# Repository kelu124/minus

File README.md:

# minus

**A minimal, single-channel, low-cost, open-source ultrasound pulse-echo platform —
built as a conference-workshop badge.**

`minus` drives one piezo transducer with a high-voltage pulse, amplifies and digitizes
the returning echo, and streams the raw data to a host. It is designed to be **cheap,
small, simple, and hackable** — a badge attendees can use in an ultrasound-conference
workshop (e.g. **muscle-contraction monitoring**, A-/M-mode) and then extend and
experiment with (coded excitation, on-device DSP, add-on boards).

> ⚠️ **Status: early design.** This repository currently holds the **requirements,
> a survey of comparable systems, a component trade study, and reference designs** —
> not yet a finished board. Non-clinical, for **research / education / NDT** only;
> not a medical device.

## What it is (at a glance)

- **MCU:** Raspberry Pi **RP2350** — precise pulse timing + fast ADC capture via PIO.
- **Signal:** **3–4 MHz** piezo (provided with the kit), **raw RF** A-mode + M-mode.
- **Front end:** unipolar HV pulser (bipolar option) → T/R switch → VGA/TGC → external
  high-speed ADC. Reuses proven blocks from the author's open boards.
- **Badge:** on-board **USB-C** (host + power), **RGB LED + small OLED** for standalone
  display, **Raspberry-Pi 40-pin** extension header, transducer via **SMA / header / uFL**,
  friendly silkscreen + test points, OSHWA certification planned.
- **Open:** open hardware + firmware + host software; designed for JLCPCB fabrication.

## Repository map

| Path | What's there |
|------|--------------|
| [`requirements.md`](requirements.md) | The design requirements (MoSCoW), with open decisions. |
| [`analysis.md`](analysis.md) | Architecture analysis — integrated vs external-ADC routes; pulser and gain options. |
| [`options.md`](options.md) + [`options_prices.csv`](options_prices.csv) | Component trade study (pulser / gain / ADC) with LCSC-referenced pricing. |
| [`systems/`](systems/README.md) | Survey of ~19 comparable ultrasound systems (datasheets, literature, by-IC index). |
| [`design/`](design/README.md) | Reference design files (un0rick, lit3rick, pic0rick, Open Echo, BioGAP shield). |
| [`pdfs/`](pdfs/README.md) | Source papers and component datasheets. |
| [`docs/claude/`](docs/claude/README.md) | Working notes: session logs, decision memory, TODO/DONE, changelog. |

## Lineage & credits

`minus` builds on the open single-channel ultrasound work of **Luc Jonveaux (kelu124)** —
[echomods/Murgen](https://github.com/kelu124/echomods),
[un0rick](https://github.com/kelu124/un0rick),
[lit3rick](https://github.com/kelu124/lit3rick), and
[pic0rick](https://github.com/kelu124/pic0rick) — reusing their proven building blocks
to reduce risk. See [`systems/`](systems/README.md) for the broader field survey.

## License

Intended to be released as **open hardware + open software** (OSHWA certification
planned), following the licensing of the boards above.

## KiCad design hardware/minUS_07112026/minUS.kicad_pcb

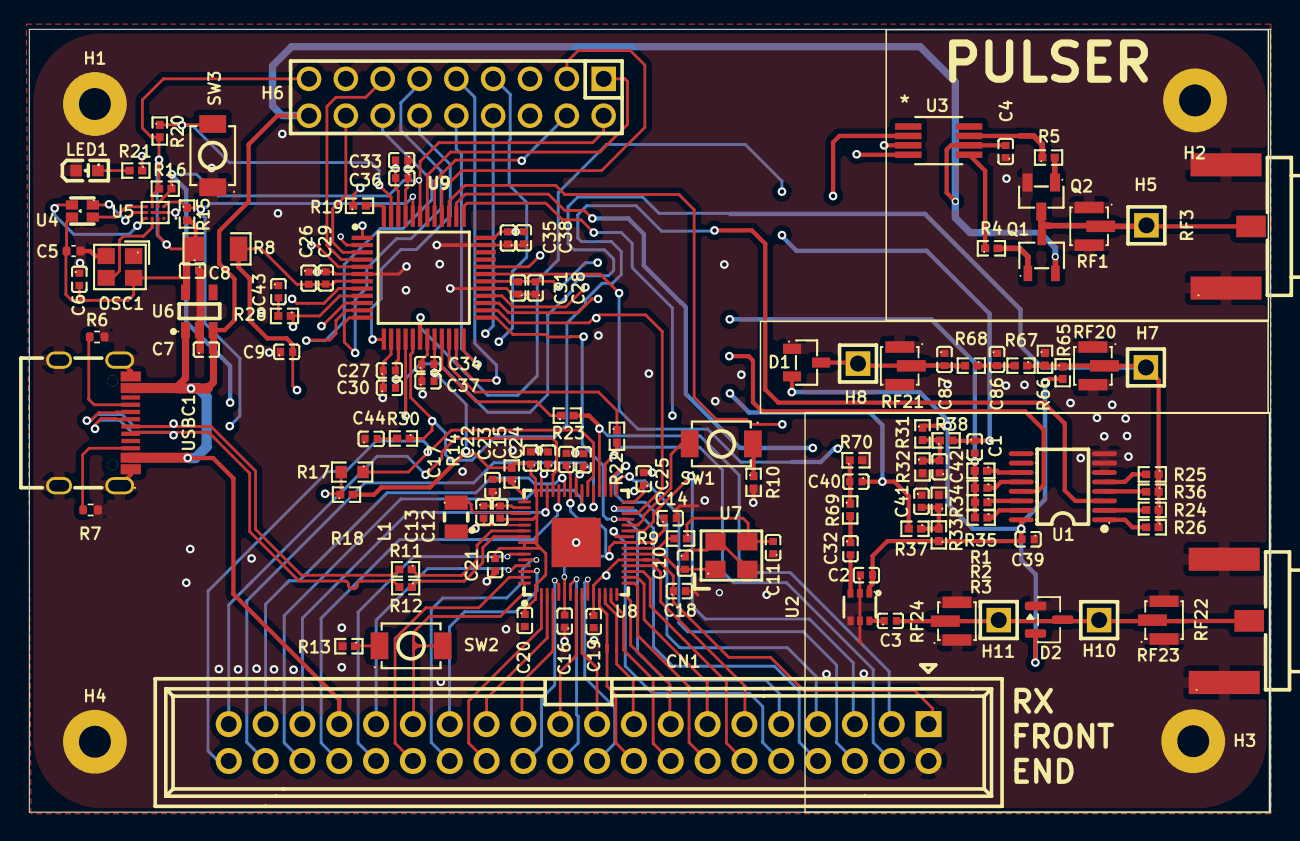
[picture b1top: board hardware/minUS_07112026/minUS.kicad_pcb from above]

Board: 4 copper layers, 85.6 x 54.0 mm, 126 parts (0 on the bottom side), 110 nets.

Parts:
C1, C3, C32, C40: CSA0402C0G331J500GT; C0402
C2: CC0402KRX7R9BB471; C0402
C4, C7, C8, C9: 1uF; C0402
C5: 4u7; C_0402_1005Metric
C6: 10nF; C0402
C10, C11: 15pF; C0402
C12, C13, C16, C17: 4.7uF; C0402
C14, C15, C18, C19, C20, C21, C22, C23, C24, C25, C26, C27, C28, C33, C34, C35, C39, C41, C42, C43, C44: 100nF; C0402
C29, C30, C31, C36, C37, C38: 1nF; C0402
C86, C87: 56pF; C0402
CN1: X9555WV-2X20-6TV01; IDC-TH_40P-P2.54_X9555WV-2X20-6TV01
D1: BAT54S_C916425; SOT-23-3_L2.9-W1.3-P1.90-LS2.4-BR
D2: BAV99; SOT-23
H1, H2, H3, H4: MountingHole_Pad; MountingHole_2.2mm_M2_Pad
H5, H7, H8, H10, H11: PZ254V-11-01P; HDR-TH_1P-P2.54-V-M
H6: PZ254V-12-18P; HDR-TH_18P-P2.54-V-M-R2-C9-S2.54
L1: 3.3uH; IND-SMD_L2.0-W1.6_AOTA-B201610S3R3-101-T
LED1: KT-0603R; LED-SMD_L1.6-W0.8-R-RD
OSC1: SX2M32.768KM20F30TNN; OSC-SMD_4P-L2.5-W2.0-BL
Q1: IRLML2244TRPBF; SOT-23-3_L2.9-W1.6-P1.90-LS2.8-BR
Q2: IRLML6244TRPBF; SOT-23-3_L2.9-W1.3-P1.90-LS2.4-BR
R1, R26: RC0402FR-072K2L; R0402
R2, R25: RC0402FR-074K7L; R0402
R3, R24: FRC0402F6801TS; R0402
R4, R5: 10Ω; R0402
R6, R7: 5K1; R_0402_1005Metric
R8: 0Ω; R1206
R9, R10, R13: 1kΩ; R0402
R11, R12: 22Ω; R0402
R14: 33Ω; R0402
R15, R16, R18, R20, R31, R32, R33, R34, R35, R36, R37, R38, R65, R66, R69, R70: 10KΩ; R0402
R17: 4.7kΩ; R0603
R19: 442Ω; R0402
R21: 330Ω; R0402
R22, R23: 0Ω; R0402
R28, R30: 1KΩ; R0402
R67, R68: 100Ω; R0402
RF1, RF20, RF21, RF23, RF24: CONUFL001-SMD-T; IPEX-SMD_3P-L2.6-W2.6-LS3.0
RF3, RF22: 132414; SMA-SMD_132414
SW1, SW2, SW3: TS-1088-AR02016; SW-SMD_L3.9-W3.0-P4.45
U1: SN74HC4052PWR; TSSOP-16_L5.0-W4.3-P0.65-LS6.4-BL
U2: BGA2817,115; SC-70-6_L2.0-W1.3-P0.65-LS2.1-BR
U3: TC4427AEUA713; MSOP8_MC_MCH-M
U4: A-SP1943B1GHR6C-C01-2T; LED-SMD_4P-L1.6-W1.5-BL_A-SP1943B1GHR6C-C01-2T
U5: LP5562TMX/NOPB; DSBGA-12_L1.7-W1.3-R3-C4-P0.40-TL
U6: AP2112K-3.3TRG1; SOT-25-5_L2.9-W1.6-P0.95-LS2.8-BL
U7: 12MHz; OSC-SMD_4P-L3.2-W2.5-BL_SIT8008BI
U8: RP2354A; QFN-60_L7.0-W7.0-P0.40-TL-EP3.4
U9: PIC32AK1216GC41048-I_PT; QFP50P900X900X120-48N
USBC1: TYPE-C-31-M-12; USB-C_SMD-TYPE-C-31-M-12_1

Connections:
+1.1V: C13.2, C14.1, C15.1, C16.2, L1.2, U8.6 (DVDD), U8.23 (DVDD), U8.39 (DVDD), U8.50 (VREG_FB)
+3V3_AVDD: C2.2, C9.2, C26.2, C29.2, C39.2, D1.2 (K), D2.2, R8.2, R31.1, R33.1, R65.2, U1.16 (VCC), U2.1 (VCC), U9.7 (AVDD)
+3V3_DVDD: C5.2, C6.2, C8.2, C12.2, C18.1, C19.1, C20.1, C21.1, C22.1, C23.1, C24.1, C25.1, C27.2, C28.2, C30.2, C31.2, C33.2, C34.2, C35.2, C36.2, C37.2, C38.2, CN1.1, H6.17, OSC1.4 (VDD), R8.1, R14.2, R15.2, R16.2, R18.2, R20.2, U4.3, U5.A2 (VDD), U5.C3 (EN/VCC), U6.5 (VOUT), U8.1 (IOVDD), U8.11 (IOVDD), U8.20 (IOVDD), U8.30 (IOVDD), U8.38 (IOVDD), U8.44 (ADC_AVDD), U8.45 (IOVDD), U8.49 (VREG_VIN), U8.53 (USB_OTP_VDD), U8.54 (QSPI_IOVDD), U9.15 (VDD_1), U9.20 (VDD_2), U9.30 (VDD_3), U9.36 (VDD_4), U9.46 (VDD_5)
+5.0V: C4.2, C7.2, CN1.33, H6.18, Q1.2 (S), U3.6, U6.1 (VIN), U6.3 (EN), USBC1.A4B9 (VBUS), USBC1.B4A9 (VBUS)
/PIC32/MCLR: R19.2, U9.48 (~MCLR)
/RP2354A/BOOT: SW1.1, U8.26 (RUN)
/RP2354A/USB_DN: R11.1, U8.51 (USB_DM)
/RP2354A/USB_DP: R12.1, U8.52 (USB_DP)
B: U4.4, U5.A4 (B)
G: U4.1, U5.B4 (G)
GND: C2.1, C4.1, C5.1, C6.1, C7.1, C8.1, C9.1, C10.1, C11.1, C12.1, C13.1, C14.2, C15.2, C16.1, C17.1, C18.2, C19.2, C20.2, C21.2, C22.2, C23.2, C24.2, C25.2, C26.1, C27.1, C28.1, C29.1, C30.1, C31.1, C33.1, C34.1, C35.1, C36.1, C37.1, C38.1, C39.1, C41.1, C42.1, C43.1, C44.1, C86.1, C87.1, CN1.2, D1.1 (A), D2.1, H1.1 (1_1), H2.1 (1_1), H3.1 (1_1), H4.1 (1_1), H6.15, LED1.2 (K), OSC1.2 (GND), Q2.2 (S), R6.2, R7.2, R10.2, R13.2, R32.2, R34.2, R66.1, R70.2, RF1.2, RF1.3, RF3.1, RF3.3, RF3.4, RF3.5, RF20.2, RF20.3, RF21.2, RF21.3, RF22.1, RF22.3, RF22.4, RF22.5, RF23.2, RF23.3, RF24.2, RF24.3, SW3.2, U1.6 (~E), U1.7 (VEE), U1.8 (GND), U2.2 (GND2), U2.4 (GND1), U2.5 (GND2), U3.3, U5.B1 (ADDR_SEL1), U5.B2 (ADDR_SEL0), U5.B3 (GND), U6.2 (GND), U7.2 (GND), U7.4 (GND), U8.47 (VREG_PGND), U8.61 (EP), U9.6 (AVSS), U9.14 (VSS_1), U9.19 (VSS_2), U9.29 (VSS_3), U9.35 (VSS_4), U9.45 (VSS_5), USBC1.1 (EH), USBC1.2 (EH), USBC1.3 (EH), USBC1.4 (EH), USBC1.A1B12 (GND), USBC1.B1A12 (GND)
unnamed: C11.2, R9.1, U7.3
unnamed: C32.1, R69.2
unnamed: C41.2, R33.2, R34.1, R37.1
unnamed: C42.2, R31.2, R32.1, R38.1
unnamed: C43.2, R28.2
unnamed: C44.2, R30.2
unnamed: C86.2, R67.2, R68.1
unnamed: LED1.1 (A), R21.2
unnamed: OSC1.3 (OUTPUT), U5.A3 (CLK_32K)
unnamed: Q1.1 (G), R4.2
unnamed: Q2.1 (G), R5.2
unnamed: R4.1, U3.5
unnamed: R5.1, U3.7
unnamed: R10.1, SW1.2
unnamed: R13.1, SW2.2
unnamed: R17.2, R18.1, R19.1
unnamed: R1.1, U1.12 (1Y0)
unnamed: R2.1, U1.14 (1Y1)
unnamed: R3.1, U1.15 (1Y2)
unnamed: R35.1, U1.11 (1Y3)
unnamed: R26.2, U1.1 (2Y0)
unnamed: R25.2, U1.5 (2Y1)
unnamed: R24.2, U1.2 (2Y2)
unnamed: R36.2, U1.4 (2Y3)
unnamed: C3.1, U2.6 (RF_IN)
unnamed: C32.2, U2.3 (RF_OUT)
unnamed: C17.2, R14.1, U8.46 (VREG_AVDD)
unnamed: L1.1, U8.48 (VREG_LX)
unnamed: H6.9, U9.23 (AD1ANN2/AD1AN8/RP23/RB6)
unnamed: H6.13, U9.4 (AD2AN9/ISRC3/IBIAS3/RP9/RA8)
unnamed: H6.10, U9.24 (AD2ANN2/AD2AN8/RP24/IOMF0/RB7)
unnamed: H6.6, U9.28 (OSCI/CLKI/RP34/IOMF6/RC1)
unnamed: H6.5, U9.27 (OSCO/CLKO/RP33/IOMF5/RC0)
unnamed: H6.16, U9.3 (PGC2/DACOUT1/AD1AN7/AD2AN3/CMP1D/CMP2D/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)
unnamed: R21.1, U9.32 (RP38/PWM4L/RC5)
unnamed: R20.1, SW3.1, U9.47 (RP53/PCI22/RD4)
unnamed: H6.4, U9.41 (RP54/ASCL1/RD5)
unnamed: H6.1, U9.42 (RP55/ASDA1/RD6)
unnamed: H6.3, U9.40 (TDI/RP52/PWM1L/IOMD5/RD3)
unnamed: R6.1, USBC1.A5 (CC1)
unnamed: R7.1, USBC1.B5 (CC2)
OA1IN+: C40.1, R37.2, U9.10 (OA1IN+/AD1AN1/CMP1B/RP5/RA4)
OA1IN-: R28.1, U1.13 (1Z), U9.9 (OA1IN-/AD1ANN1/AD2AN0/RP4/RA3)
OA1OUT: C1.2, R1.2, R2.2, R3.2, R35.2, U9.8 (OA1OUT/AD1AN0/CMP1A/RP3/RA2)
OA2IN+: C1.1, R38.2, U9.18 (OA2IN+/AD2AN4/CMP2B/RP19/RB2)
OA2IN-: R30.1, U1.3 (2Z), U9.17 (TMS/OA2IN-/AD1AN4/AD2ANN1/RP18/RB1)
OA2OUT: H7.1 (1_1), R24.1, R25.1, R26.1, R36.1, R65.1, R66.2, R67.1, RF20.1, U9.16 (OA2OUT/AD2AN1/CMP2A/RP17/INT0/RB0)
OA3IN+: H6.12, U9.13 (OA3IN+/AD2AN2/CMP3B/RP22/RB5)
OA3IN-: H6.11, U9.12 (OA3IN-/AD1AN2/RP7/RA6)
OA3OUT: H6.14, U9.11 (OA3OUT/AD1AN3/CMP3A/RP6/RA5)
PGC1: R22.1, U9.22 (PGC1/AD2AN5/CMP2C/ISRC1/IBIAS1/RP21/SCL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)
PGD1: R23.1, U9.21 (PGD1/AN1P5/CMP1C/ISRC0/IBIAS0/RP20/SDA1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)
PIC32_ADC: C87.2, D1.3, H8.1 (1_1), R68.2, RF21.1, U9.5 (AD1ANN3/AD1AN9/RP10/RA9)
QSPI_SCLK: CN1.28, U8.56 (QSPI_SCLK)
QSPI_SD0: CN1.31, U8.57 (QSPI_SD0)
QSPI_SD1: CN1.30, U8.59 (QSPI_SD1)
QSPI_SD2: CN1.27, U8.58 (QSPI_SD2)
QSPI_SD3: CN1.32, U8.55 (QSPI_SD3)
QSPI_SS: CN1.29, SW2.1, U8.60 (QSPI_SS)
R: U4.2, U5.C4 (R)
RDY: CN1.20, U8.10 (GPIO7), U9.2 (AD1AN6/RP8/IOMF1/RA7)
RP2354 PIO-PWM_H: CN1.18, U3.2, U8.12 (GPIO8)
RP2354 PIO-PWM_L: CN1.17, U3.4, U8.13 (GPIO9)
RP2354_PWM: CN1.13, U8.17 (GPIO13)
RP_GPIO10: CN1.16, U8.14 (GPIO10)
RP_GPIO14: CN1.12, U8.18 (GPIO14)
RP_GPIO15: CN1.11, U8.19 (GPIO15)
RP_GPIO18: CN1.8, U8.29 (GPIO18)
RP_GPIO19: CN1.6, U8.31 (GPIO19)
RP_GPIO20: CN1.7, U8.32 (GPIO20)
RP_GPIO21: CN1.4, R22.2, U8.33 (GPIO21)
RP_GPIO22: CN1.3, R23.2, U8.34 (GPIO22)
RP_GPIO23: CN1.38, U8.35 (GPIO23)
RP_GPIO24: CN1.40, R17.1, U8.36 (GPIO24)
RP_GPIO25: CN1.36, U8.37 (GPIO25)
RP_GPIO26: CN1.37, U8.40 (GPIO26_ADC0)
RP_GPIO27: CN1.34, U8.41 (GPIO27_ADC1)
RP_GPIO28: CN1.39, U8.42 (GPIO28_ADC2)
RP_GPIO29: CN1.35, U8.43 (GPIO29_ADC3)
RX_NODE: C40.2, R69.1, R70.1
SCL: CN1.25, H6.2, R16.1, U5.C2 (SCL), U8.3 (GPIO1), U9.43 (RP56/ASCL2/IOMD7/IOMF4/RD7)
SDA: CN1.26, R15.1, U5.C1 (SDA), U8.2 (GPIO0), U9.44 (RP57/ASDA2/IOMD6/IOMF3/RD8)
SPI_CLK: CN1.23, U8.4 (GPIO2), U9.38 (TCK/RP50/PWM2L/IOMD3/RD1)
SPI_CS: CN1.21, U8.8 (GPIO5), U9.37 (RP49/PWM2H/IOMD2/RD0)
SPI_CS1: CN1.15, U8.15 (GPIO11)
SPI_CS2: CN1.14, U8.16 (GPIO12)
SPI_MISO: CN1.22, U8.7 (GPIO4), U9.31 (PGC3/RP35/PWM4H/RC2)
SPI_MOSI: CN1.24, U8.5 (GPIO3), U9.39 (TDO/RP51/PWM1H/IOMD4/RD2)
SWCLK: CN1.10, U8.24 (SWCLK)
SWDIO: CN1.5, U8.25 (SWDIO)
TRANSDUCER: C3.2, D2.3, H10.1 (1_1), H11.1 (1_1), RF22.2, RF23.1, RF24.1
TRIG: CN1.19, U8.9 (GPIO6), U9.1 (PGD2/AD2AN6/CMP3C/ISRC2/IBIAS2/RP1/SDA2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)
Transducer: H5.1 (1_1), Q1.3 (D), Q2.3 (D), RF1.1, RF3.2
UART_RX: H6.8, U8.28 (GPIO17), U9.26 (RP40/RC7)
UART_TX: CN1.9, H6.7, U8.27 (GPIO16), U9.25 (RP39/RC6)
USB_D+: R12.2, USBC1.A6 (DP1), USBC1.B6 (DP2)
USB_D-: R11.2, USBC1.A7 (DN1), USBC1.B7 (DN2)
XIN: C10.2, U7.1, U8.21 (XIN)
XOUT: R9.2, U8.22 (XOUT)

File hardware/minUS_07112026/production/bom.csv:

Designator,Footprint,Quantity,Value,LCSC Part #
"C1, C3, C32, C40",C0402,4,CSA0402C0G331J500GT,C48642894
"C10, C11",C0402,2,15pF,C326803
"C12, C13, C16, C17",C0402,4,4.7uF,C5718966
"C14, C15, C18, C19, C20, C21, C22, C23, C24, C25, C26, C27, C28, C33, C34, C35, C39, C41, C42, C43, C44",C0402,21,100nF,C152814
C2,C0402,1,CC0402KRX7R9BB471,C106207
"C29, C30, C31, C36, C37, C38",C0402,6,1nF,C14442
"C4, C7, C8, C9",C0402,4,1uF,C52923
C5,0402,1,4u7,C326586
C6,C0402,1,10nF,C15195
"C86, C87",C0402,2,56pF,C526981
CN1,IDC-TH_40P-P2.54_X9555WV-2X20-6TV01,1,X9555WV-2X20-6TV01,C2884558
D1,SOT-23-3_L2.9-W1.3-P1.90-LS2.4-BR,1,BAT54S_C916425,C916425
D2,SOT-23,1,BAV99,C2500
"H10, H11, H5, H7, H8",HDR-TH_1P-P2.54-V-M,5,PZ254V-11-01P,C492400
H6,HDR-TH_18P-P2.54-V-M-R2-C9-S2.54,1,PZ254V-12-18P,C492426
L1,IND-SMD_L2.0-W1.6_AOTA-B201610S3R3-101-T,1,3.3uH,C42411119
LED1,LED-SMD_L1.6-W0.8-R-RD,1,KT-0603R,C2286
OSC1,OSC-SMD_4P-L2.5-W2.0-BL,1,SX2M32.768KM20F30TNN,C2901603
Q1,SOT-23-3_L2.9-W1.6-P1.90-LS2.8-BR,1,IRLML2244TRPBF,C169763
Q2,SOT-23-3_L2.9-W1.3-P1.90-LS2.4-BR,1,IRLML6244TRPBF,C143946
"R1, R26",R0402,2,RC0402FR-072K2L,C114762
"R10, R13, R9",R0402,3,1kΩ,C2906864
"R11, R12",R0402,2,22Ω,C2929994
R14,R0402,1,33Ω,C2906931
"R15, R16, R18, R20, R31, R32, R33, R34, R35, R36, R37, R38, R65, R66, R69, R70",R0402,16,10KΩ,C25744
R17,R0603,1,4.7kΩ,C99782
R19,R0402,1,442Ω,C453691
"R2, R25",R0402,2,RC0402FR-074K7L,C105871
R21,R0402,1,330Ω,C105875
"R22, R23",R0402,2,0Ω,C844673
"R24, R3",R0402,2,FRC0402F6801TS,C2906876
"R28, R30",R0402,2,1KΩ,C11702
"R4, R5",R0402,2,10Ω,C138066
"R6, R7",0402,2,5K1,C105873
"R67, R68",R0402,2,100Ω,C25076
R8,R1206,1,0Ω,C2907406
"RF1, RF20, RF21, RF23, RF24",IPEX-SMD_3P-L2.6-W2.6-LS3.0,5,CONUFL001-SMD-T,C22418213
"RF22, RF3",SMA-SMD_132414,2,132414,C6363889
"SW1, SW2, SW3",SW-SMD_L3.9-W3.0-P4.45,3,TS-1088-AR02016,C720477
U1,TSSOP-16_L5.0-W4.3-P0.65-LS6.4-BL,1,SN74HC4052PWR,C22449643
U2,SC-70-6_L2.0-W1.3-P0.65-LS2.1-BR,1,"BGA2817,115",C2654187
U3,MSOP8_MC_MCH-M,1,TC4427AEUA713,C628548
U4,LED-SMD_4P-L1.6-W1.5-BL_A-SP1943B1GHR6C-C01-2T,1,A-SP1943B1GHR6C-C01-2T,C19171342
U5,DSBGA-12_L1.7-W1.3-R3-C4-P0.40-TL,1,LP5562TMX/NOPB,C544465
U6,SOT-25-5_L2.9-W1.6-P0.95-LS2.8-BL,1,AP2112K-3.3TRG1,C51118
U7,OSC-SMD_4P-L3.2-W2.5-BL_SIT8008BI,1,12MHz,C20625731
U8,QFN-60_L7.0-W7.0-P0.40-TL-EP3.4,1,RP2354A,C41378174
U9,QFP50P900X900X120-48N,1,PIC32AK1216GC41048-I_PT,C46545915
USBC1,USB-C_SMD-TYPE-C-31-M-12_1,1,TYPE-C-31-M-12,C165948

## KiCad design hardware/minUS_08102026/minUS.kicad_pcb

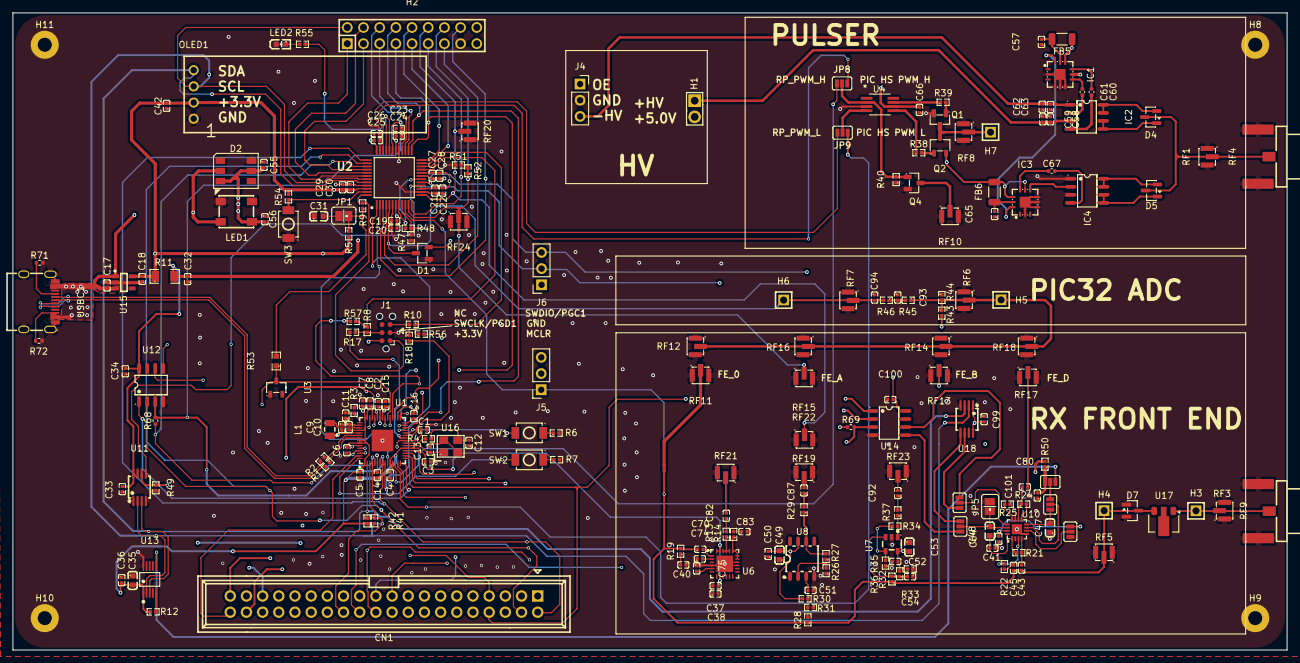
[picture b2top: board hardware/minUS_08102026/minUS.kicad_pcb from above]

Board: 4 copper layers, 200.0 x 100.0 mm, 222 parts (0 on the bottom side), 159 nets.

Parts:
C1, C2, C3, C4, C5, C6, C7, C8, C15, C16, C20, C21, C23, C25, C27, C29, C33, C34, C36, C37, C38, C41, C42, C50, C51, C52, C54, C55, C56, C57, C59, C63, C65, C70, C74, C75, C80, C82, C83, C87, C92, C99, C100, C101: 100nF; C0402
C9, C10, C11, C14: 4.7uF; C0402
C12, C13: 15pF; C0402
C17, C18, C32, C58, C62, C64, C66: 1uF; C0402
C19, C22, C24, C26, C28, C30: 1nF; C0402
C31: 470nF; C0603
C35, C49, C53: 10uF; C0603
C40: 47pF; C0402
C43, C45: 330nF; C0402
C47, C48: 2.2uF; C0603
C60, C61, C67: 10nF; C_0402_1005Metric
C93, C94: 56pF; C0402
CN1: X9555WV-2X20-6TV01; IDC-TH_40P-P2.54_X9555WV-2X20-6TV01
D1: BAT54S_C916425; SOT-23-3_L2.9-W1.3-P1.90-LS2.4-BR
D2: WS2812; LED_WS2812_PLCC6_5.0x5.0mm_P1.6mm
D4, D5, D7: BAV99; SOT-23
FB5, FB6: 120Ohm 3 A; L_1206_3216Metric
H1: PZ254V-11-02P; HDR-TH_2P-P2.54-V-M
H2: PZ254V-12-18P; HDR-TH_18P-P2.54-V-M-R2-C9-S2.54
H3, H4, H5, H6, H7: PZ254V-11-01P; HDR-TH_1P-P2.54-V-M
H8, H9, H10, H11: MountingHole_Pad; MountingHole_2.2mm_M2_Pad
IC1, IC3: MD1213K6-G; QFN-12_L4.0-W4.0-P0.80-BL-EP1.7
IC2, IC4: TC6320TG-G; SOIC-8_L4.9-W3.9-P1.27-LS6.0-BL
J1: Conn_ARM_SWD_TagConnect_TC2030-NL; Tag-Connect_TC2030-IDC-NL_2x03_P1.27mm_Vertical
J4, J5, J6: Conn_01x03_Pin; PinSocket_1x03_P2.54mm_Vertical
JP1, JP5: Jumper_2_Bridged; JUMPER_SMD_1x2
JP2, JP3, JP4, JP6, JP7, JP8, JP9: Jumper_3_Open; Jumper_3_NO
L1: 3.3uH; IND-SMD_L2.0-W1.6_AOTA-B201610S3R3-101-T
LED1: SK6812_C5378720; LED-SMD_4P-L5.4-W5.0_SK6812
LED2: KT-0603R; LED-SMD_L1.6-W0.8-R-RD
NT1, NT2: NetTie_2; NetTie-2_SMD_Pad0.5mm
OLED1: HS91L02W2C01; OLED-TH_L38.0-W12.0_HS91L02W2C01
Q1: IRLML6244TRPBF; SOT-23-3_L2.9-W1.3-P1.90-LS2.4-BR
Q2: IRLML2244TRPBF; SOT-23-3_L2.9-W1.6-P1.90-LS2.8-BR
Q4: 2N7002_C916396; SOT-23-3_L2.9-W1.3-P1.90-LS2.4-BR
R1, R2: 22Ω; R0402
R3: 33Ω; R0402
R4, R6, R7: 1kΩ; R0402
R5, R30, R31, R32, R33, R40, R41, R42, R43, R44, R48, R50, R52, R54: 10KΩ; R0402
R8, R10: 47Ω; R0402
R9: 442Ω; R0402
R11: 0Ω; R1206
R12: 100KΩ; R0402
R13, R14: 20Ω; R0402
R17, R18, R21, R22, R24, R25, R56, R57: 0Ω; R0402
R19: 15Ω; R0402
R26: 39.2Ω; R0402
R27: 750Ω; R0402
R28, R29, R36, R37: 50Ω; R0402
R34: 240Ω; R0402
R35: 27Ω; R0402
R38, R39: 10Ω; R0402
R45, R46: 100Ω; R0402
R47, R49, R51: 1KΩ; R0402
R53: 4.7kΩ; R0603
R55: 330Ω; R0402
R68, R69: 100R; R_0402_1005Metric
R71, R72: 5K1; R_0402_1005Metric
RF1, RF3, RF5, RF6, RF7, RF8, RF10, RF11, RF12, RF13, RF14, RF15, RF16, RF17, RF18, RF19, RF20, RF21, RF22, RF23, RF24: CONUFL001-SMD-T; IPEX-SMD_3P-L2.6-W2.6-LS3.0
RF4, RF9: 132414; SMA-SMD_132414
SW1, SW2, SW3: TS-1088-AR02016; SW-SMD_L3.9-W3.0-P4.45
U1: RP2354A; QFN-60_L7.0-W7.0-P0.40-TL-EP3.4
U2: PIC32AK1216GC41048-I_PT; QFP50P900X900X120-48N
U3: BAT54_C22466368; SOT-23-3_L2.9-W1.4-P1.90-LS2.5-BR
U4: TC4427AEUA713; MSOP8_MC_MCH-M
U6: AD8432ACPZ-R7; LFCSP-24_L4.0-W4.0-P0.50-BL-EP
U7: LMH6629MFX/NOPB; SOT-23-5_L2.9-W1.6-P0.95-LS2.8-BR
U8: OPA847IDR; SOIC-8_L4.9-W3.9-P1.27-LS6.0-TL
U10: AD8338ACPZ-RL; LFCSP-16_L3.0-W3.0-P0.50-BL-EP1.6
U11, U18: MCP4531-103E/MS; MSOP-8_L3.0-W3.0-P0.65-LS5.0-BL
U12, U14: MCP4131-104E/SN; SOIC-8_L4.9-W3.9-P1.27-LS6.0-BL
U13: MCP4728A0T-E/UN; MSOP-10_L3.0-W3.0-P0.50-LS5.0-BL
U15: AP2112K-3.3TRG1; SOT-25-5_L2.9-W1.6-P0.95-LS2.8-BL
U16: 12MHz; OSC-SMD_4P-L3.2-W2.5-BL_SIT8008BI
U17: MD0100N8-G; SOT-89-3
USBC1: TYPE-C-31-M-12; USB-C_SMD-TYPE-C-31-M-12_1

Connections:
+1.1V: C1.1, C2.1, C9.2, C14.2, L1.2, U1.6 (DVDD), U1.23 (DVDD), U1.39 (DVDD), U1.50 (VREG_FB)
+3V3_AVDD: C19.2, C20.2, C32.2, C33.2, C34.2, C64.2, C99.2, C100.2, D1.2 (K), JP2.3 (B), R11.2, R43.2, U2.7 (AVDD), U10.15 (VBAT), U11.8 (VDD), U12.8 (VDD), U14.8 (VDD), U18.1 (HVCA0), U18.8 (VDD)
+3V3_DVDD: C3.1, C4.1, C5.1, C6.1, C7.1, C8.1, C10.2, C15.1, C16.1, C18.2, C21.2, C22.2, C23.2, C24.2, C25.2, C26.2, C27.2, C28.2, C29.2, C30.2, C35.2, C36.2, C37.2, C38.1, C42.2, H2.17, J1.2 (VCC), OLED1.2 (VCC), R3.2, R5.2, R11.1, R12.1, R41.2, R42.2, R54.2, U1.1 (IOVDD), U1.11 (IOVDD), U1.20 (IOVDD), U1.30 (IOVDD), U1.38 (IOVDD), U1.44 (ADC_AVDD), U1.45 (IOVDD), U1.49 (VREG_VIN), U1.53 (USB_OTP_VDD), U1.54 (QSPI_IOVDD), U2.15 (VDD_1), U2.20 (VDD_2), U2.30 (VDD_3), U2.36 (VDD_4), U2.46 (VDD_5), U6.8 (VPS2), U6.23 (VPS1), U6.24 (ENB), U13.1 (VDD), U15.5 (VOUT)
+5.0V: C17.2, C49.2, C50.2, C52.2, C53.2, C55.2, C56.2, C66.2, D2.3 (VCC), D2.5 (VDD), FB5.1, FB6.1, H1.2, H2.18, IC1.8 (VH), IC1.10 (VDD2), IC3.8 (VH), IC3.10 (VDD2), LED1.3 (VDD), Q2.2 (S), R30.2, R32.2, U4.6, U7.5 (V+), U8.7 (+VS), U15.1 (VIN), U15.3 (EN), USBC1.A4B9 (VBUS), USBC1.B4A9 (VBUS)
+HV: C58.2, C59.2, H1.1, IC2.3 (SP)
-HV: C62.2, C63.2, IC2.1 (SN), J4.3
/PIC32/MCLR: J1.1 (~RESET), R9.2, U2.48 (~MCLR)
/RP2354A/BOOT: SW1.1, U1.26 (RUN)
/RP2354A/USB_DN: R2.1, U1.51 (USB_DM)
/RP2354A/USB_DP: R1.1, U1.52 (USB_DP)
FE_0_OUT: NT2.2, RF11.1
FE_A_OUT: J6.2, RF13.1, U2.16 (OA2OUT/AD2AN1/CMP2A/RP17/INT0/RB0), U11.5 (P0A)
FE_B_OUT: NT1.2, RF15.1
FE_D_OUT: C80.2, RF17.1
GND: C1.2, C2.2, C3.2, C4.2, C5.2, C6.2, C7.2, C8.2, C9.1, C10.1, C11.1, C12.1, C13.1, C14.1, C15.2, C16.2, C17.1, C18.1, C19.1, C20.1, C21.1, C22.1, C23.1, C24.1, C25.1, C26.1, C27.1, C28.1, C29.1, C30.1, C31.1, C32.1, C33.1, C34.1, C35.1, C36.1, C37.1, C38.2, C40.1, C41.1, C42.1, C47.1, C49.1, C50.1, C51.1, C52.1, C53.1, C54.1, C55.1, C56.1, C57.1, C58.1, C59.1, C62.1, C63.1, C64.1, C65.1, C66.1, C74.1, C75.1, C83.2, C93.1, C94.1, C99.1, C100.1, C101.1, D1.1 (A), D2.6 (VSS), D7.1, D7.2, H2.15, H8.1 (1_1), H9.1 (1_1), H10.1 (1_1), H11.1 (1_1), IC1.2 (VL), IC1.4 (GND_1), IC1.5 (VSS1), IC1.6 (VSS2), IC1.13 (GND_2), IC3.2 (VL), IC3.4 (GND_1), IC3.5 (VSS1), IC3.6 (VSS2), IC3.13 (GND_2), IC4.1 (SN), IC4.3 (SP), J1.3 (GND), J4.2, JP2.1 (A), JP5.1 (A), LED1.1 (GND), LED2.2 (K), OLED1.1 (GND), Q1.2 (S), Q4.2 (S), R6.2, R7.2, R26.1, R31.1, R33.1, R35.1, R40.1, R44.1, R47.2, R49.2, R51.2, R71.2, R72.2, RF1.2, RF1.3, RF3.2, RF3.3, RF4.1, RF4.3, RF4.4, RF4.5, RF5.2, RF5.3, RF6.2, RF6.3, RF7.2, RF7.3, RF8.2, RF8.3, RF9.1, RF9.3, RF9.4, RF9.5, RF10.2, RF10.3, RF11.2, RF11.3, RF12.2, RF12.3, RF13.2, RF13.3, RF14.2, RF14.3, RF15.2, RF15.3, RF16.2, RF16.3, RF17.2, RF17.3, RF18.2, RF18.3, RF19.2, RF19.3, RF20.2, RF20.3, RF21.2, RF21.3, RF22.2, RF22.3, RF23.2, RF23.3, RF24.2, RF24.3, SW3.2, U1.47 (VREG_PGND), U1.61 (EP), U2.6 (AVSS), U2.14 (VSS_1), U2.19 (VSS_2), U2.29 (VSS_3), U2.35 (VSS_4), U2.45 (VSS_5), U3.1 (A), U4.3, U6.4 (COMM), U6.15 (COM2), U6.16 (COM1), U6.25 (EP), U7.2 (V-), U8.4 (–VS), U10.5 (COMM), U10.17 (EP), U11.1 (HVCA0), U11.4 (VSS), U12.4 (VSS), U13.10 (VSS), U14.4 (VSS), U15.2 (GND), U16.2 (GND), U16.4 (GND), U18.4 (VSS), USBC1.1 (EH), USBC1.2 (EH), USBC1.3 (EH), USBC1.4 (EH), USBC1.A1B12 (GND), USBC1.B1A12 (GND)
MCP4531_POW: J6.3, R49.1, U2.17 (TMS/OA2IN-/AD1AN4/AD2ANN1/RP18/RB1), U11.6 (P0W)
MCP4728_VOUTA: JP4.3 (B), U13.6 (VOUTA)
unnamed: C12.2, R4.1, U16.3
unnamed: C40.2, R19.1
unnamed: C45.2, R22.2
unnamed: C82.1, R13.2
unnamed: C82.2, RF21.1
unnamed: C83.1, R14.2
unnamed: C87.1, R29.2
unnamed: C87.2, RF22.1
unnamed: C92.1, R37.2
unnamed: C92.2, RF23.1
unnamed: C93.2, R45.2, R46.1
unnamed: D4.2 (A), IC2.7 (DN_1), IC2.8 (DN_2)
unnamed: D4.3 (K), D5.3 (K), RF1.1, RF4.2
unnamed: D5.2 (A), IC4.7 (DN_1), IC4.8 (DN_2)
unnamed: H5.1 (1_1), R43.1, R44.2, R45.1, RF6.1, RF12.1, RF14.1, RF16.1, RF18.1
unnamed: C60.1, IC1.9 (OUTA)
unnamed: C61.1, IC1.7 (OUTB)
unnamed: C57.2, FB5.2, IC1.11 (VDD1)
unnamed: D4.1 (K), IC2.5 (DP_1), IC2.6 (DP_2)
unnamed: C61.2, IC2.2 (GN)
unnamed: C60.2, IC2.4 (GP)
unnamed: C67.1, IC3.9 (OUTA)
unnamed: IC3.7 (OUTB), IC4.2 (GN)
unnamed: C65.2, FB6.2, IC3.11 (VDD1)
unnamed: D5.1 (K), IC4.5 (DP_1), IC4.6 (DP_2)
unnamed: C67.2, IC4.4 (GP)
unnamed: J1.4 (SWCLK), R8.2, R17.1
unnamed: J1.5 (SWDIO), R10.2, R18.1
unnamed: C31.2, JP1.1 (A)
unnamed: JP1.2 (B), R5.1, R9.1, R53.2
unnamed: JP2.2 (C), U10.6 (MODE)
unnamed: C47.2, JP3.1 (A), U10.8 (DETO)
unnamed: JP3.3 (B), JP4.2 (C)
unnamed: JP3.2 (C), U10.7 (GAIN)
unnamed: C48.1, JP5.2 (B), JP7.2 (C), U10.14 (NOFSN)
unnamed: JP6.1 (A), U18.6 (P0W)
unnamed: JP6.3 (B), U14.6 (P0W)
unnamed: JP6.2 (C), U10.13 (VAGC)
unnamed: JP7.1 (A), U18.5 (P0A)
unnamed: JP7.3 (B), U14.5 (P0A)
unnamed: JP8.2 (C), Q4.1 (G), R40.2, U4.2
unnamed: JP9.2 (C), U4.4
unnamed: LED2.1 (A), R55.2
unnamed: Q1.1 (G), R39.2
unnamed: Q2.1 (G), R38.2
unnamed: Q4.3 (D), RF10.1
unnamed: R6.1, SW1.2
unnamed: R7.1, SW2.2
unnamed: R38.1, U4.5
unnamed: R39.1, U4.7
unnamed: CN1.3, U1.18 (GPIO14)
unnamed: CN1.5, U1.19 (GPIO15)
unnamed: CN1.11, U1.29 (GPIO18)
unnamed: CN1.13, U1.31 (GPIO19)
unnamed: CN1.15, U1.32 (GPIO20)
unnamed: CN1.21, U1.35 (GPIO23)
unnamed: CN1.25, U1.37 (GPIO25)
unnamed: CN1.27, U1.40 (GPIO26_ADC0)
unnamed: CN1.29, U1.41 (GPIO27_ADC1)
unnamed: CN1.31, U1.42 (GPIO28_ADC2)
unnamed: CN1.33, U1.43 (GPIO29_ADC3)
unnamed: C11.2, R3.1, U1.46 (VREG_AVDD)
unnamed: L1.1, U1.48 (VREG_LX)
unnamed: H2.9, U2.23 (AD1ANN2/AD1AN8/RP23/RB6)
unnamed: H2.13, U2.4 (AD2AN9/ISRC3/IBIAS3/RP9/RA8)
unnamed: H2.10, U2.24 (AD2ANN2/AD2AN8/RP24/IOMF0/RB7)
unnamed: H2.6, U2.28 (OSCI/CLKI/RP34/IOMF6/RC1)
unnamed: H2.5, U2.27 (OSCO/CLKO/RP33/IOMF5/RC0)
unnamed: H2.16, U2.3 (PGC2/DACOUT1/AD1AN7/AD2AN3/CMP1D/CMP2D/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)
unnamed: R55.1, U2.32 (RP38/PWM4L/RC5)
unnamed: R54.1, SW3.1, U2.47 (RP53/PCI22/RD4)
unnamed: H2.4, U2.41 (RP54/ASCL1/RD5)
unnamed: H2.1, U2.42 (RP55/ASDA1/RD6)
unnamed: H2.3, U2.40 (TDI/RP52/PWM1L/IOMD5/RD3)
unnamed: R13.1, U6.20 (GMH1), U6.21 (GOH1), U6.22 (OPH1)
unnamed: R14.1, U6.17 (OPL1), U6.18 (GOL1), U6.19 (GML1)
unnamed: C70.2, U6.1 (INH1)
unnamed: C74.2, U6.2 (INL1)
unnamed: C75.2, U6.5 (INL2)
unnamed: C54.2, R32.1, R33.2, R36.2, U7.3 (+IN)
unnamed: R34.1, R35.2, U7.4 (-IN)
unnamed: R34.2, R37.1, U7.1 (OUT)
unnamed: R26.2, R27.1, U8.2 (Inverting/Input)
unnamed: C51.2, R28.2, R30.1, R31.2, U8.3 (Noninverting/Input)
unnamed: R27.2, R29.1, U8.6 (Output)
unnamed: R24.2, U10.9 (FBKM)
unnamed: R25.2, U10.12 (FBKP)
unnamed: R22.1, U10.3 (INMD)
unnamed: C43.2, R21.2, U10.4 (INMR)
unnamed: R21.1, U10.1 (INPR)
unnamed: C80.1, R24.1, U10.10 (OUTM)
unnamed: R25.1, U10.11 (OUTP)
unnamed: C41.2, C48.2, U10.16 (VREF)
unnamed: R71.1, USBC1.A5 (CC1)
unnamed: R72.1, USBC1.B5 (CC2)
OA1IN+: C43.1, C45.1, C70.1, D7.3, H4.1 (1_1), J5.1, NT2.1, R19.2, R28.1, R36.1, RF5.1, U2.10 (OA1IN+/AD1AN1/CMP1B/RP5/RA4), U17.3 (B)
OA1IN-: J5.2, R47.1, R48.2, U2.9 (OA1IN-/AD1ANN1/AD2AN0/RP4/RA3)
OA1OUT: J5.3, J6.1, R48.1, U2.8 (OA1OUT/AD1AN0/CMP1A/RP3/RA2), U2.18 (OA2IN+/AD2AN4/CMP2B/RP19/RB2)
OA3IN+: H2.12, RF19.1, RF20.1, U2.13 (OA3IN+/AD2AN2/CMP3B/RP22/RB5)
OA3IN-: H2.11, R51.1, R52.2, U2.12 (OA3IN-/AD1AN2/RP7/RA6)
OA3OUT: H2.14, NT1.1, R52.1, RF24.1, U2.11 (OA3OUT/AD1AN3/CMP3A/RP6/RA5)
OE: IC1.12 (OE), IC3.12 (OE), J4.1
PGC1: R10.1, R56.1, U2.22 (PGC1/AD2AN5/CMP2C/ISRC1/IBIAS1/RP21/SCL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)
PGD1: R8.1, R57.1, U2.21 (PGD1/AN1P5/CMP1C/ISRC0/IBIAS0/RP20/SDA1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)
PIC32_ADC: C94.2, D1.3, H6.1 (1_1), R46.2, RF7.1, U2.5 (AD1ANN3/AD1AN9/RP10/RA9)
PIC HS-PWM_H: JP8.1 (A), U2.33 (PGD3/RP36/PWM3H/IOMD0/RC3)
PIC HS-PWM_L: JP9.1 (A), U2.34 (RP37/PWM3L/IOMD1/RC4)
QSPI_SCLK: CN1.35, U1.56 (QSPI_SCLK)
QSPI_SD0: CN1.38, U1.57 (QSPI_SD0)
QSPI_SD1: CN1.40, U1.59 (QSPI_SD1)
QSPI_SD2: CN1.39, U1.58 (QSPI_SD2)
QSPI_SD3: CN1.37, U1.55 (QSPI_SD3)
QSPI_SS: SW2.1, U1.60 (QSPI_SS)
RDY: CN1.20, U1.10 (GPIO7), U2.2 (AD1AN6/RP8/IOMF1/RA7)
RGB_LED: CN1.6, D2.2 (DIN), LED1.2 (DIN), U1.14 (GPIO10)
RP2354 PIO-PWM_H: CN1.16, JP8.3 (B), U1.12 (GPIO8)
RP2354 PIO-PWM_L: CN1.12, JP9.3 (B), U1.13 (GPIO9)
RP2354_PWM: CN1.1, R50.2, U1.17 (GPIO13)
RP2354_PWM+RC: C101.2, JP4.1 (A), R50.1
RP_GPIO21: CN1.17, R56.2, U1.33 (GPIO21)
RP_GPIO22: CN1.19, R57.2, U1.34 (GPIO22)
RP_GPIO24: CN1.23, R53.1, U1.36 (GPIO24), U3.3 (K)
SCL: CN1.26, H2.2, OLED1.3 (SCL), R41.1, U1.3 (GPIO1), U2.43 (RP56/ASCL2/IOMD7/IOMF4/RD7), U11.2 (SCL), U13.2 (SCL), U18.2 (SCL)
SDA: CN1.28, OLED1.4 (SDA), R42.1, U1.2 (GPIO0), U2.44 (RP57/ASDA2/IOMD6/IOMF3/RD8), U11.3 (SDA), U13.3 (SDA), U18.3 (SDA)
SPI_CLK: CN1.4, U1.4 (GPIO2), U2.38 (TCK/RP50/PWM2L/IOMD3/RD1), U12.2 (SCK), U14.2 (SCK)
SPI_CS: CN1.2, U1.8 (GPIO5), U2.37 (RP49/PWM2H/IOMD2/RD0)
SPI_CS1: CN1.14, U1.15 (GPIO11), U12.1 (~CS)
SPI_CS2: CN1.8, U1.16 (GPIO12), U14.1 (~CS)
SPI_MISO: CN1.22, R68.2, R69.2, U1.7 (GPIO4), U2.31 (PGC3/RP35/PWM4H/RC2), U12.3 (SDI/SDO), U14.3 (SDI/SDO)
SPI_MOSI: CN1.24, R68.1, R69.1, U1.5 (GPIO3), U2.39 (TDO/RP51/PWM1H/IOMD4/RD2)
SWCLK: R17.2, U1.24 (SWCLK)
SWDIO: R18.2, U1.25 (SWDIO)
TRANSDUCER: H3.1 (1_1), RF3.1, RF9.2, U17.1 (A)
TRIG: CN1.18, U1.9 (GPIO6), U2.1 (PGD2/AD2AN6/CMP3C/ISRC2/IBIAS2/RP1/SDA2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)
Transducer: H7.1 (1_1), Q1.3 (D), Q2.3 (D), RF8.1
UART_RX: CN1.9, H2.8, U1.28 (GPIO17), U2.26 (RP40/RC7)
UART_TX: CN1.7, H2.7, U1.27 (GPIO16), U2.25 (RP39/RC6)
USB_D+: R1.2, USBC1.A6 (DP1), USBC1.B6 (DP2)
USB_D-: R2.2, USBC1.A7 (DN1), USBC1.B7 (DN2)
XIN: C13.2, U1.21 (XIN), U16.1
XOUT: R4.2, U1.22 (XOUT)
~MCP4728_BSY: R12.2, U13.5 (RDY/~BSY)

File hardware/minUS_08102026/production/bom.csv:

Designator,Footprint,Quantity,Value,LCSC Part #
"C1, C100, C101, C15, C16, C2, C20, C21, C23, C25, C27, C29, C3, C33, C34, C36, C37, C38, C4, C41, C42, C5, C50, C51, C52, C54, C55, C56, C57, C59, C6, C63, C65, C7, C70, C74, C75, C8, C80, C82, C83, C87, C92, C99",C0402,44,100nF,C152814
"C10, C11, C14, C9",C0402,4,4.7uF,C5718966
"C12, C13",C0402,2,15pF,C326803
"C17, C18, C32, C58, C62, C64, C66",C0402,7,1uF,C52923
"C19, C22, C24, C26, C28, C30",C0402,6,1nF,C14442
C31,C0603,1,470nF,C1623
"C35, C49, C53",C0603,3,10uF,C96446
C40,C0402,1,47pF,C1567
C43,C0402,1,330nF,C19271634
"C47, C48",C0603,2,2.2uF,C23630
"C60, C61, C67",0402,3,10nF,C15195
"C93, C94",C0402,2,56pF,C526981
CN1,IDC-TH_40P-P2.54_X9555WV-2X20-6TV01,1,X9555WV-2X20-6TV01,C2884558
D1,SOT-23-3_L2.9-W1.3-P1.90-LS2.4-BR,1,BAT54S_C916425,C916425
D2,LED_WS2812_PLCC6_5.0x5.0mm_P1.6mm,1,WS2812,C42417498
"D4, D5, D7",SOT-23,3,BAV99,C2500
"FB5, FB6",1206,2,120Ohm 3 A,C98293
H1,HDR-TH_2P-P2.54-V-M,1,PZ254V-11-02P,C492401
H2,HDR-TH_18P-P2.54-V-M-R2-C9-S2.54,1,PZ254V-12-18P,C492426
"H3, H4, H5, H6, H7",HDR-TH_1P-P2.54-V-M,5,PZ254V-11-01P,C492400
"IC1, IC3",QFN-12_L4.0-W4.0-P0.80-BL-EP1.7,2,MD1213K6-G,C621434
"IC2, IC4",SOIC-8_L4.9-W3.9-P1.27-LS6.0-BL,2,TC6320TG-G,C624992
"J4, J5, J6",PinSocket_1x03_P2.54mm_Vertical,3,Conn_01x03_Pin, C49257
L1,IND-SMD_L2.0-W1.6_AOTA-B201610S3R3-101-T,1,3.3uH,C42411119
LED1,LED-SMD_4P-L5.4-W5.0_SK6812,1,SK6812_C5378720,C5378720
LED2,LED-SMD_L1.6-W0.8-R-RD,1,KT-0603R,C2286
OLED1,OLED-TH_L38.0-W12.0_HS91L02W2C01,1,HS91L02W2C01,C5248081
Q1,SOT-23-3_L2.9-W1.3-P1.90-LS2.4-BR,1,IRLML6244TRPBF,C143946
Q2,SOT-23-3_L2.9-W1.6-P1.90-LS2.8-BR,1,IRLML2244TRPBF,C169763
Q4,SOT-23-3_L2.9-W1.3-P1.90-LS2.4-BR,1,2N7002_C916396,C916396
"R1, R2",R0402,2,22Ω,C2929994
"R10, R8",R0402,2,47Ω,C137973
R11,R1206,1,0Ω,C2907406
R12,R0402,1,100KΩ,C25741
"R13, R14",R0402,2,20Ω,C138031
"R17, R18, R56, R57",R0402,4,0Ω,C844673
R19,R0402,1,15Ω,C138052
R26,R0402,1,39.2Ω,C42372094
R27,R0402,1,750Ω,C25132
"R28, R29, R36, R37",R0402,4,50Ω,C51048227
R3,R0402,1,33Ω,C2906931
"R30, R31, R32, R33, R40, R41, R42, R43, R44, R48, R5, R50, R52, R54",R0402,14,10KΩ,C25744
R34,R0402,1,240Ω,C114755
R35,R0402,1,27Ω,C25156
"R38, R39",R0402,2,10Ω,C138066
"R4, R6, R7",R0402,3,1kΩ,C2906864
"R45, R46",R0402,2,100Ω,C25076
"R47, R49, R51",R0402,3,1KΩ,C11702
R53,R0603,1,4.7kΩ,C99782
R55,R0402,1,330Ω,C105875
"R68, R69",0402,2,100R,C106232 
"R71, R72",0402,2,5K1,C105873
R9,R0402,1,442Ω,C453691
"RF1, RF10, RF11, RF12, RF13, RF14, RF15, RF16, RF17, RF18, RF19, RF20, RF21, RF22, RF23, RF24, RF3, RF5, RF6, RF7, RF8",IPEX-SMD_3P-L2.6-W2.6-LS3.0,21,CONUFL001-SMD-T,C22418213
"RF4, RF9",SMA-SMD_132414,2,132414,C6363889
"SW1, SW2, SW3",SW-SMD_L3.9-W3.0-P4.45,3,TS-1088-AR02016,C720477
U1,QFN-60_L7.0-W7.0-P0.40-TL-EP3.4,1,RP2354A,C41378174
U10,LFCSP-16_L3.0-W3.0-P0.50-BL-EP1.6,1,AD8338ACPZ-RL,C652715
"U11, U18",MSOP-8_L3.0-W3.0-P0.65-LS5.0-BL,2,MCP4531-103E/MS,C150808
"U12, U14",SOIC-8_L4.9-W3.9-P1.27-LS6.0-BL,2,MCP4131-104E/SN,C636034
U13,MSOP-10_L3.0-W3.0-P0.50-LS5.0-BL,1,MCP4728A0T-E/UN,C627341
U15,SOT-25-5_L2.9-W1.6-P0.95-LS2.8-BL,1,AP2112K-3.3TRG1,C51118
U16,OSC-SMD_4P-L3.2-W2.5-BL_SIT8008BI,1,12MHz,C20625731
U17,SOT-89-3,1,MD0100N8-G,C629131
U2,QFP50P900X900X120-48N,1,PIC32AK1216GC41048-I_PT,C46545915
U3,SOT-23-3_L2.9-W1.4-P1.90-LS2.5-BR,1,BAT54_C22466368,C22466368
U4,MSOP8_MC_MCH-M,1,TC4427AEUA713,C628548
U6,LFCSP-24_L4.0-W4.0-P0.50-BL-EP,1,AD8432ACPZ-R7,C652837
U7,SOT-23-5_L2.9-W1.6-P0.95-LS2.8-BR,1,LMH6629MFX/NOPB,C2059678
U8,SOIC-8_L4.9-W3.9-P1.27-LS6.0-TL,1,OPA847IDR,C2870028
USBC1,USB-C_SMD-TYPE-C-31-M-12_1,1,TYPE-C-31-M-12,C165948
